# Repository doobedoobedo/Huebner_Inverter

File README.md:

# inverter-hardware
KiCAD port from eagle source files for Johannes Huebner's inverter main board v1.2 (https://github.com/jsphuebner/inverter-hardware)
See https://openinverter.org

Porting was greatly helped by the eagle-to-kicad scripts available from https://github.com/lachlanA/eagle-to-kicad

# License
Attribution-ShareAlike 4.0 International
https://creativecommons.org/licenses/by-sa/4.0/legalcode

You musn't change the copyright info (J. Huebner and openinverter.org) on the silkscreen in size location or content.

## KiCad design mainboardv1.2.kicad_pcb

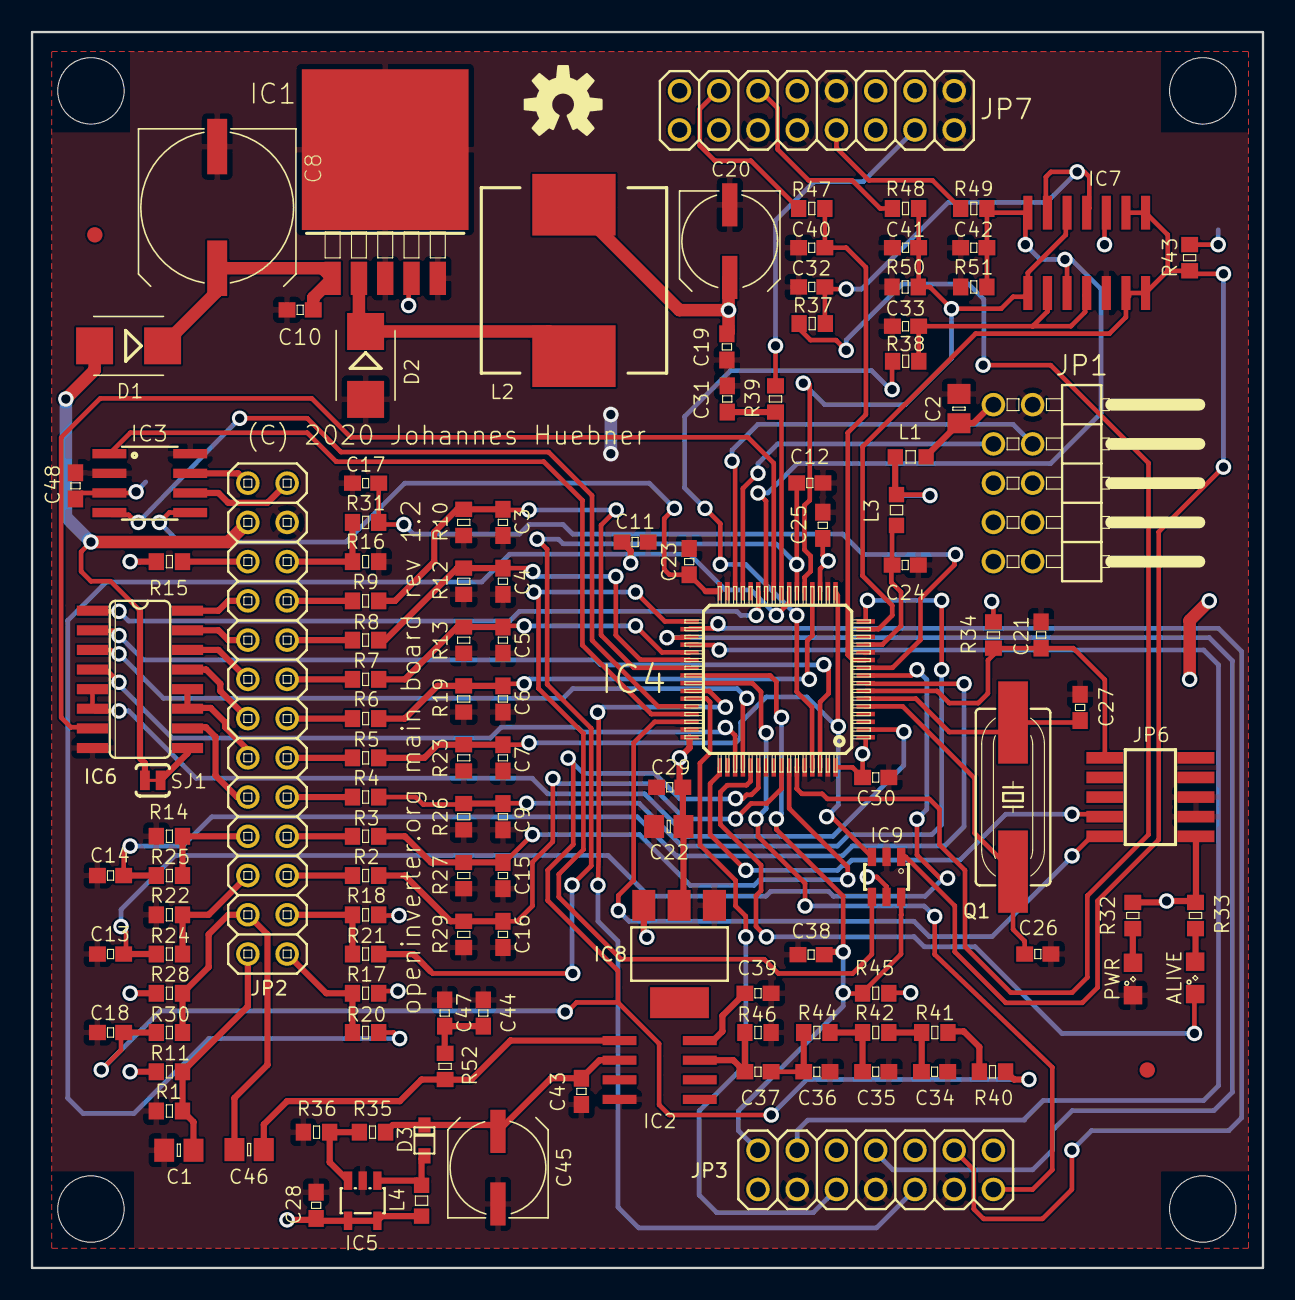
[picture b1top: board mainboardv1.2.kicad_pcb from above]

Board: 2 copper layers, 79.7 x 80.0 mm, 133 parts (0 on the bottom side), 97 nets.

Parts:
ALIVE70: LED_0603_GN; LED_SML0805
C1, C2, C22, C46: 10~; RCL_C0805
C3, C4, C5, C6, C7, C9, C10, C13, C14, C15, C16, C17, C19, C21, C23, C24, C25, C28, C29, C30, C31, C32, C33, C39, C40, C43, C48: 1~; RCL_C0603
C8: 680~; RCL_UD-10X10_NICHICON
C11, C12, C18, C38, C41, C42: 1nF; RCL_C0603
C20, C45: 470~; RCL_UD-6_3X7_7_NICHICON
C26, C27: 20p; RCL_C0603
C34, C35, C36, C37, C44, C47: 22n; RCL_C0603
D1, D2: CDBA540-HF; DIODE_SMB
D3: SBR1A40S3-7; ADAFRUIT_SOD-323F
FID1, FID2: FIDUCIAL1X2.5; SPARKFUN-AESTHETICS_FIDUCIAL-1X2.5
H1, H2, H3, H4: MountingHole; MountingHole_4.3mm_M4
IC1: LM2596S; NATIONAL-SEMICONDUCTOR_TO263-5
IC2: TDA2822D; ST-MICROELECTRONICS_SO08
IC3: MCP2562P; SPARKFUN-DIGITALIC_SO08
IC4: STM32F103RBT6; STM32_TQFP64
IC5: MIC2288YD5; ADAFRUIT_SOT23-5L
IC6: ULN2003AD; ULN-UDN_SO16
IC7: LM2901; LINEAR_SO14
IC8: REG1117; BURR-BROWN_SOT223
IC9: SN74LVC1G10; 74XX-EU_SOT23-6
JP1: PINHEAD_2X05_90
JP2: PINHEAD_2X13
JP3: PINHEAD_2X07
JP6: CON-LEOTRONICS_1365-10
JP7: PINHEAD_2X08
L1, L3, L4: 10~H; RCL_L2012C
L2: 47~H; SPARKFUN-PASSIVES_CDRH125
LOGO1: OSHW-LOGOM; SPARKFUN-AESTHETICS_OSHW-LOGO-M
PWR70: LED_0603_GN; LED_SML0805
Q1: 8MHz; CRYSTAL_HC49UP
R1: 220; RCL_R0603
R2, R3, R4, R6, R7, R8, R9, R35, R42, R44, R48, R49: 3k3; RCL_R0603
R5, R50, R51: 4k7; RCL_R0603
R10, R12, R13, R19, R23, R26, R27, R29: 1k2; RCL_R0603
R11: 120R/510R; RCL_R0603
R14, R20, R21, R22, R24, R25, R30, R31, R34, R37, R38, R39, R41, R43, R45, R46, R47: 10k; RCL_R0603
R15, R16, R17, R18, R28, R32, R33, R36, R40: 510; RCL_R0603
R52: 10R; RCL_R0603
SJ1: SOLDERJUMPERTRACE; SPARKFUN-PASSIVES_SJ_2S-TRACE
svg2mod: G***; copyright_mask

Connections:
+12V: D1.A, JP2.24, SJ1.2
/CANH: IC3.7, JP2.26
/CANL: IC3.6, JP2.25
/ENC_A/S2: JP2.3, R18.2, R21.2
/ENC_B/S3: JP2.1, R17.2, R20.2
/ENC_Z/R1: C46.2, JP2.4, R28.2, R30.2
/I_L1: JP7.6, R48.1
/I_L2: JP7.9, R49.1
/MTEMP+: JP2.22, R15.1
/MTEMP-: JP2.21, R16.1, R31.1
/N$1: IC6.9, SJ1.1
/N$2: C27.1, IC4.6, Q1.1
/N$4: C26.1, IC4.5, Q1.2
/N$6: IC4.46, JP6.2
/N$7: C24.2, IC4.13, L3.1
/N$9: IC4.49, JP6.4
/N$10: C33.1, IC7.9, IC7.11, R38.2
/N$11: C44.2, C47.2, R52.1
/N$12: R40.2, R41.1
/N$14: D2.C, IC1.2, L2.1
/N$15: C32.1, IC7.4, IC7.6, R37.2
/N$17: C35.1, R42.2, R44.1
/N$18: C36.1, C37.1, R44.2
/N$19: C37.2, IC2.7, R46.2
/N$20: C46.1, IC2.1, R52.2
/N$21: C43.2, C45.+, D3.C, IC2.2, R35.2
/N$22: PWR70.A, R32.2
/N$23: ALIVE70.A, R33.2
/N$24: IC5.3, R35.1, R36.2
/N$25: C8.+, C10.1, D1.C, IC1.1
/N$26: D3.A, IC5.1, L4.2
/N$27: C39.2, IC2.8
/N$28: C2.1, JP1.1, L1.2
/N$30: C34.1, R41.2, R42.1
/NRST: C21.1, IC4.7, JP6.10, R34.1
/OUT_BRAKE: IC6.10, JP2.10
/OUT_DCSW: IC6.11, IC6.12, JP2.12
/OUT_ERR: IC6.13, JP2.14
/OUT_OVTMP: IC6.14, JP2.16
/OUT_PRE: IC6.16, JP2.20
/OUT_TEMP: IC6.15, JP2.18
/PA1/TIM2_CH2: IC4.15, IC7.1, IC7.2, IC7.13, IC7.14, IC9.1, R43.1
/PA2/ADC2: C9.1, IC4.16, R4.2, R26.2
/PA3/ADC3: C7.1, IC4.17, IC9.3, R5.2, R23.2
/PA4/ADC4: C6.1, IC4.20, R6.2, R19.2
/PA5/ADC5: C41.1, IC4.21, IC7.5, IC7.8, R48.2, R50.2
/PA6/TIM3_CH1: C12.1, IC4.22, R21.1
/PA7/TIM3_CH2: C11.1, IC4.23, R20.1
/PA8/TIM1_CH1: IC4.41, JP3.2
/PA9/TIM1_CH2: IC4.42, JP3.6
/PA10/TIM1_CH3: IC4.43, JP3.10
/PA11/CANRX: IC3.4, IC4.44
/PA12/CANTX: IC3.1, IC4.45
/PB0/ADC8: C42.1, IC4.26, IC7.7, IC7.10, R49.2, R51.2
/PB1/ADC9: IC4.27, IC6.1
/PB5: C16.1, IC4.57, R2.2, R29.2
/PB6/TIM4_CH1: C15.1, IC4.58, R3.2, R27.2
/PB7/TIM4_CH2: IC4.59, R37.1
/PB8/TIM4_CH3: IC4.61, R38.1
/PB9/TIM4_CH4: IC4.62, IC6.2
/PB10/USART3_TX: IC4.29, JP1.3
/PB11/USART3_RX: IC4.30, JP1.4
/PB12/TIM1_BKIN: IC4.33, IC9.4
/PC0/ADC10: C14.1, IC4.8, R25.2
/PC1/ADC11: C13.1, IC4.9, R24.2
/PC2/ADC12: C17.1, IC4.10, R31.2
/PC3/ADC13: C40.1, IC4.11, R47.2
/PC4/ADC14: C31.1, IC4.24, R39.1
/PC5/ADC15: IC4.25, IC6.7
/PC6: C5.1, IC4.37, R7.2, R13.2
/PC7: C4.1, IC4.38, R8.2, R12.2
/PC8: C3.1, IC4.39, R9.2, R10.2
/PC9: C38.1, IC4.40, IC9.6, JP3.13, R45.1
/PC10: IC4.51, IC6.4
/PC11: IC4.52, IC6.3
/PC12: ALIVE70.C, IC4.53
/PC13: IC4.2, IC6.5, IC6.6
/PD2/TIM3_ETR: C18.1, IC4.54, R30.1, R40.1
/S4/S1: C1.1, JP2.2, R1.2, R11.1
/SIG_BMS: JP2.19, R9.1
/SIG_BRAKE: JP2.9, R4.1
/SIG_CRUISE: JP2.5, R2.1
/SIG_EMCYSTOP: JP2.17, R8.1
/SIG_FORWARD: JP2.13, R6.1
/SIG_MPROT: JP2.11, R5.1
/SIG_REVERSE: JP2.15, R7.1
/SIG_START: JP2.7, R3.1
/THROTTLE1: JP2.6, R22.2, R24.1
/THROTTLE2: JP2.8, R14.2, R25.1
/TIM1_CH1N: IC4.34, JP3.3
/TIM1_CH2N: IC4.35, JP3.7
/TIM1_CH3N: IC4.36, JP3.11
/TMPHS: JP7.13, R39.2
/UDC: JP7.4, R47.1
GND: C1.2, C2.2, C3.2, C4.2, C5.2, C6.2, C7.2, C8.-, C9.2, C10.2, C11.2, C12.2, C13.2, C14.2, C15.2, C16.2, C17.2, C18.2, C19.2, C20.-, C21.2, C22.2, C23.1, C24.1, C25.1, C26.2, C27.2, C28.2, C29.1, C30.1, C31.2, C32.2, C33.2, C34.2, C35.2, C36.2, C38.2, C39.1, C40.2, C41.2, C42.2, C43.1, C44.1, C45.-, C47.1, C48.2, D2.A, IC1.3, IC1.5, IC1.6, IC2.4, IC3.2, IC3.8, IC4.12, IC4.18, IC4.31, IC4.47, IC4.60, IC4.63, IC5.2, IC6.8, IC7.12, IC8.1, IC9.2, JP1.2, JP2.23, JP3.4, JP3.8, JP3.12, JP6.3, JP6.5, JP7.5, JP7.7, JP7.10, JP7.15, JP7.16, PWR70.C, R1.1, R10.1, R12.1, R13.1, R14.1, R16.2, R19.1, R22.1, R23.1, R26.1, R27.1, R29.1, R36.1, R46.1, R50.1, R51.1
VCC: C19.1, C20.+, C28.1, C48.1, IC1.4, IC3.3, IC5.4, IC5.5, IC7.3, IC8.3, JP3.1, JP3.5, JP3.9, JP7.1, JP7.2, JP7.8, JP7.11, JP7.12, L2.2, L4.1, R11.2, R15.2, R17.1, R18.1, R28.1, R43.2, R45.2
VCCIO: C22.1, C23.2, C25.2, C29.2, C30.2, IC3.5, IC4.1, IC4.19, IC4.32, IC4.48, IC4.64, IC8.2, IC9.5, JP6.1, L1.1, L3.2, R32.1, R33.1, R34.2

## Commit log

2020-01-05 missed silkscreen for IC9
2020-01-05 mounting holes and keepout areas around
2020-01-05 mounting holes
2020-01-05 tweaked copper fill zone settings
2020-01-12 Added copyright notice to mask

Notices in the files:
mainboardv1.2.kicad_pcb:
(C) 2020 Johannes Huebner
